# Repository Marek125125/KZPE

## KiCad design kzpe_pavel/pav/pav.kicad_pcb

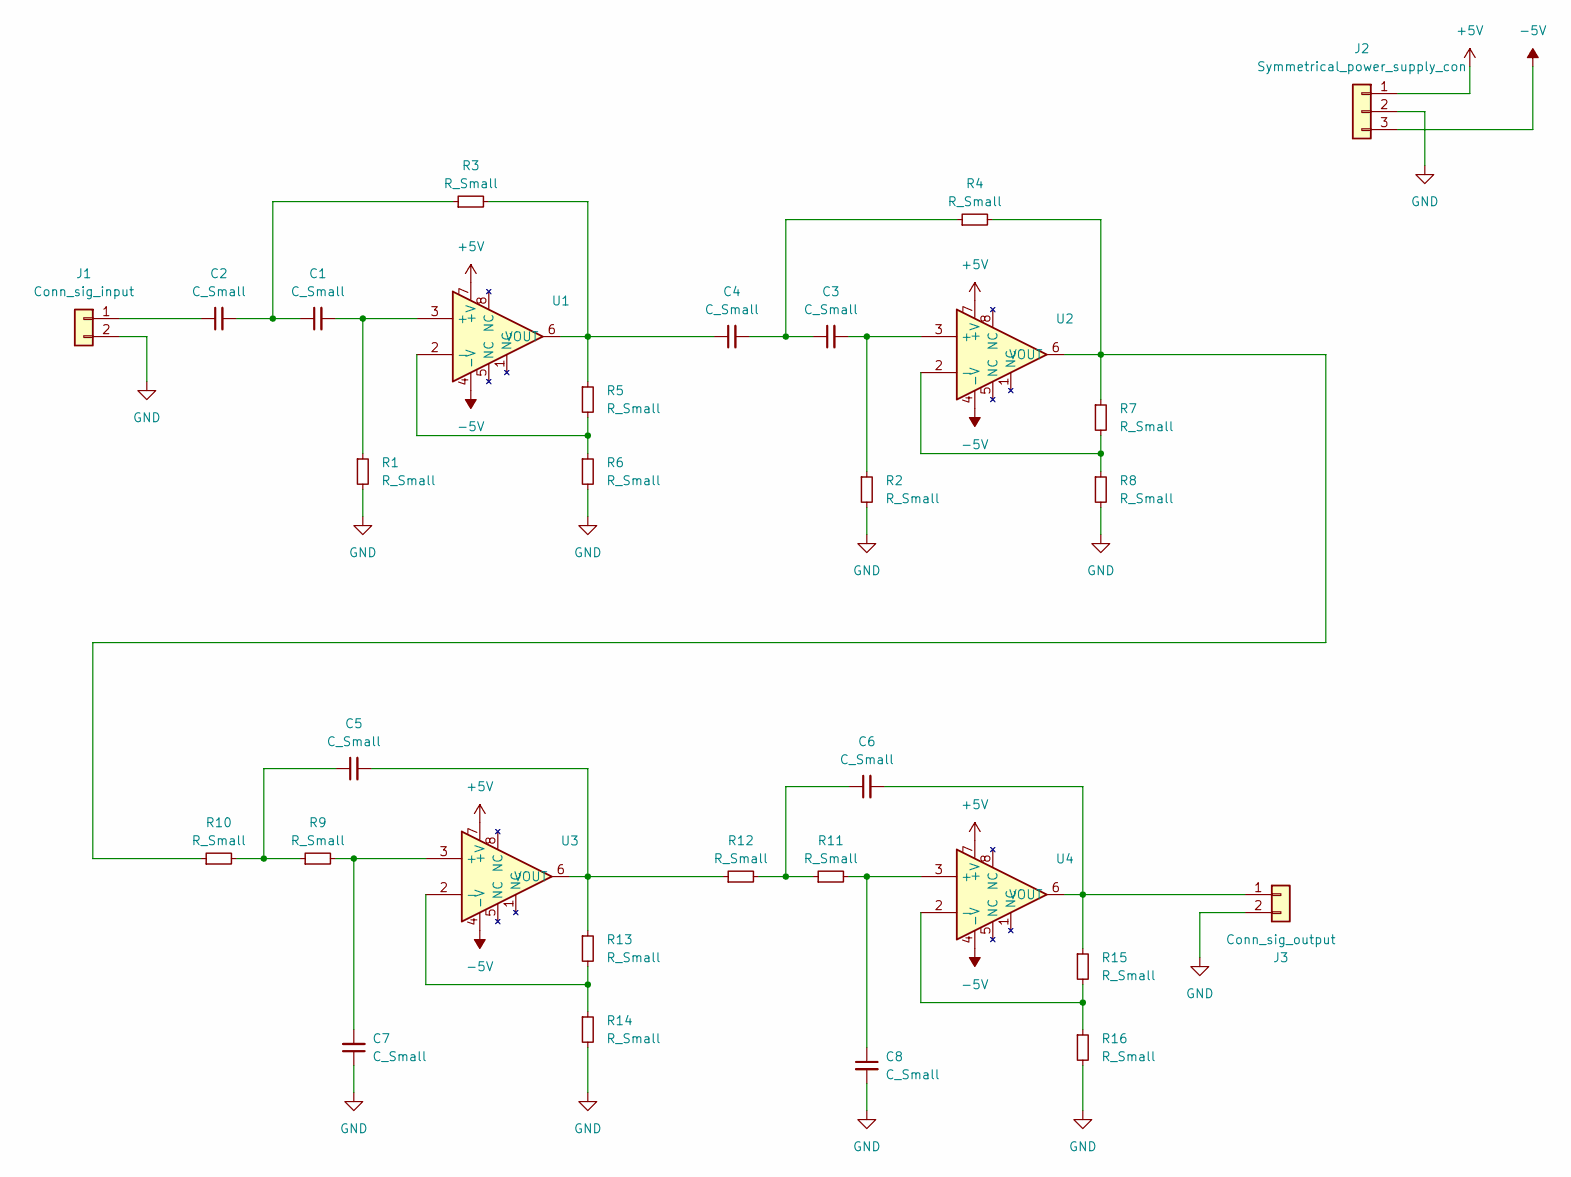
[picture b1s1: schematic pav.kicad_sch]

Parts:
C1, C2, C3, C4, C5, C6, C7, C8: C_Small; CP_Radial_D4.0mm_P2.00mm
J1: Conn_sig_input; JWT_A3963_1x02_P3.96mm_Vertical
J2: Symmetrical_power_supply_con; JST_EH_B3B-EH-A_1x03_P2.50mm_Vertical
J3: Conn_sig_output; JWT_A3963_1x02_P3.96mm_Vertical
R1, R2, R3, R4, R5, R6, R7, R8, R9, R10, R11, R12, R13, R14, R15, R16: R_Small; R_Axial_DIN0204_L3.6mm_D1.6mm_P7.62mm_Horizontal
U1, U2, U3, U4: DIP794W56P254L959H533Q8N

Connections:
+5V: J2.1, U1.7 (+V), U2.7 (+V), U3.7 (+V), U4.7 (+V)
-5V: J2.3, U1.4 (-V), U2.4 (-V), U3.4 (-V), U4.4 (-V)
GND: C7.1, C8.2, J1.2, J2.2, J3.2, R1.2, R2.2, R6.2, R8.2, R14.2, R16.2
unnamed: C1.1, C2.2, R3.1
unnamed: C3.1, C4.2, R4.1
unnamed: C5.1, R9.1, R10.2
unnamed: C6.1, R11.1, R12.2
unnamed: C2.1, J1.1
unnamed: C6.2, J3.1, R15.1, U4.6 (VOUT)
unnamed: C1.2, R1.1, U1.3 (+)
unnamed: C4.1, R3.2, R5.1, U1.6 (VOUT)
unnamed: C3.2, R2.1, U2.3 (+)
unnamed: R7.2, R8.1, U2.2 (-)
unnamed: R4.2, R7.1, R10.1, U2.6 (VOUT)
unnamed: C7.2, R9.2, U3.3 (+)
unnamed: R13.2, R14.1, U3.2 (-)
unnamed: C5.2, R12.1, R13.1, U3.6 (VOUT)
unnamed: C8.1, R11.2, U4.3 (+)
unnamed: R15.2, R16.1, U4.2 (-)

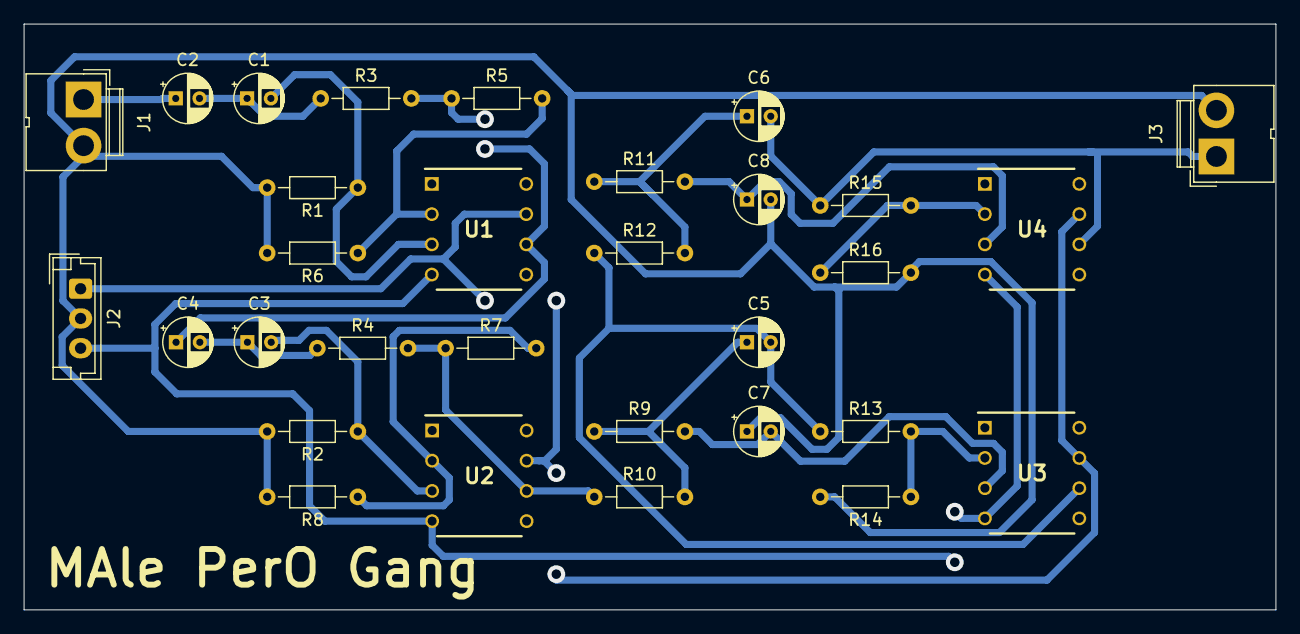
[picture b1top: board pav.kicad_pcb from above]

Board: 2 copper layers, 105.2 x 49.2 mm, 31 parts (0 on the bottom side), 19 nets.

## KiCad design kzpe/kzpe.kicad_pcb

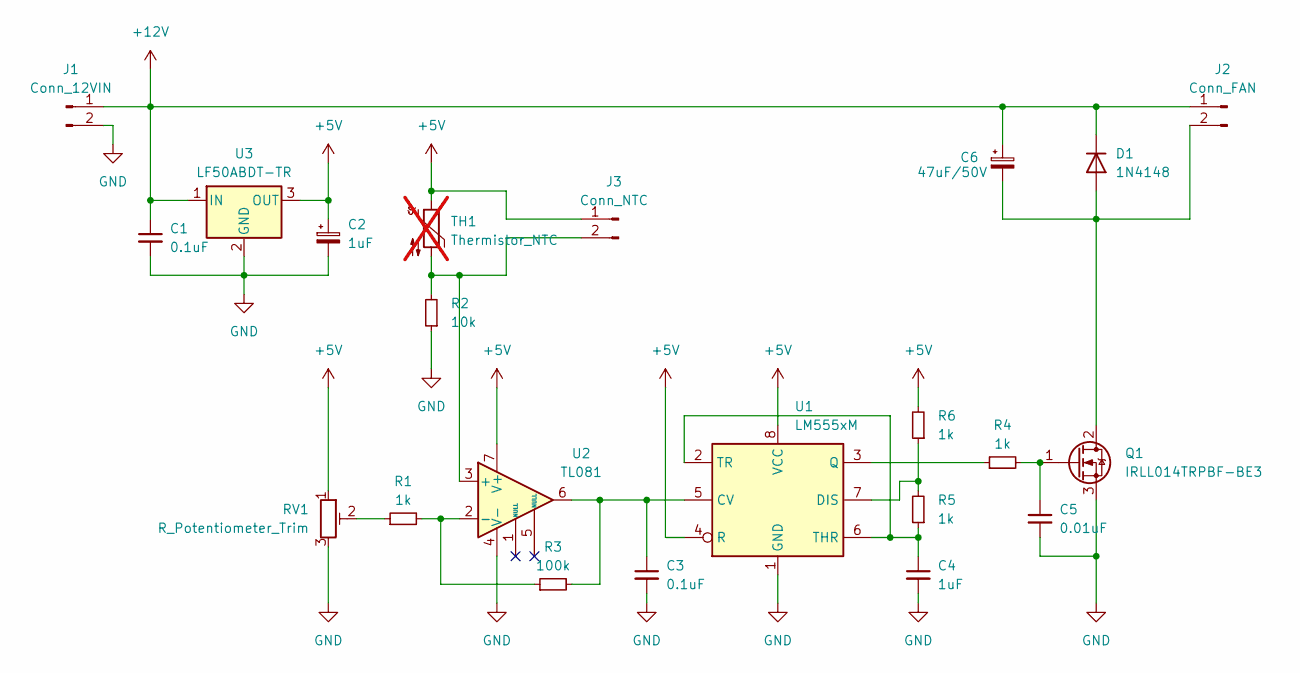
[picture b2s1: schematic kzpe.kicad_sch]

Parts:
C1, C3: 0.1uF; C_0402_1005Metric
C2, C4: 1uF; C_0402_1005Metric
C5: 0.01uF; C_0402_1005Metric
C6: 47uF/50V; CP_Elec_4x4.5
D1: 1N4148; D_0402_1005Metric
J1: Conn_12VIN; SolderWire-1.5sqmm_1x02_P6mm_D1.7mm_OD3mm
J2: Conn_FAN; SolderWire-1.5sqmm_1x02_P6mm_D1.7mm_OD3mm
J3: Conn_NTC; SolderWire-1.5sqmm_1x02_P6mm_D1.7mm_OD3mm
Q1: IRLL014TRPBF-BE3; SOT230P700X180-4N
R1, R4, R5, R6: 1k; R_0402_1005Metric
R2: 10k; R_0402_1005Metric
R3: 100k; R_0402_1005Metric
RV1: R_Potentiometer_Trim; Potentiometer_Bourns_3224J_Horizontal
TH1: Thermistor_NTC; R_0402_1005Metric; not fitted
U1: LM555xM; SOIC127P600X175-8N
U2: TL081; SOIC127P600X175-8N
U3: LF50ABDT-TR; TO228P972X240-3N

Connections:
+5V: C2.1, J3.1, R6.2, RV1.1, TH1.1, U1.4 (R), U1.8 (VCC), U2.7 (V+), U3.3 (OUT)
+12V: C1.1, C6.1, D1.1 (K), J1.1, J2.1, U3.1 (IN)
GND: C1.2, C2.2, C3.2, C4.2, C5.2, J1.2, Q1.3 (S), R2.1, RV1.3, U1.1 (GND), U2.4 (V-), U3.2 (GND)
unnamed: C6.2, D1.2 (A), J2.2, Q1.2 (D)
unnamed: J3.2, R2.2, TH1.2, U2.3 (+)
unnamed: C5.1, Q1.1 (G), R4.2
unnamed: R1.1, RV1.2
unnamed: C3.1, R3.2, U1.5 (CV), U2.6
unnamed: R5.2, R6.1, U1.7 (DIS)
unnamed: R4.1, U1.3 (Q)
unnamed: C4.1, R5.1, U1.2 (TR), U1.6 (THR)
unnamed: R1.2, R3.1, U2.2 (-)

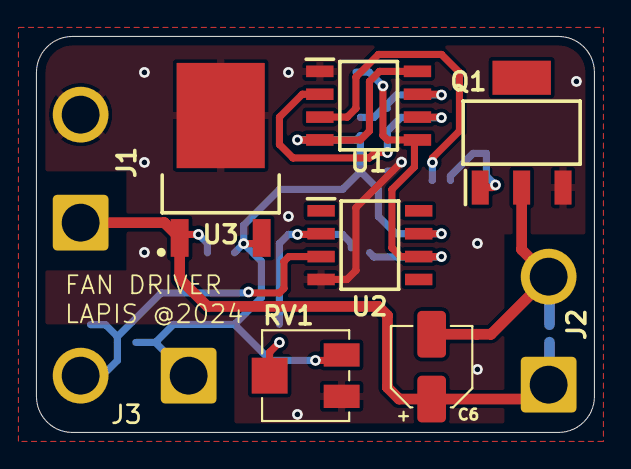
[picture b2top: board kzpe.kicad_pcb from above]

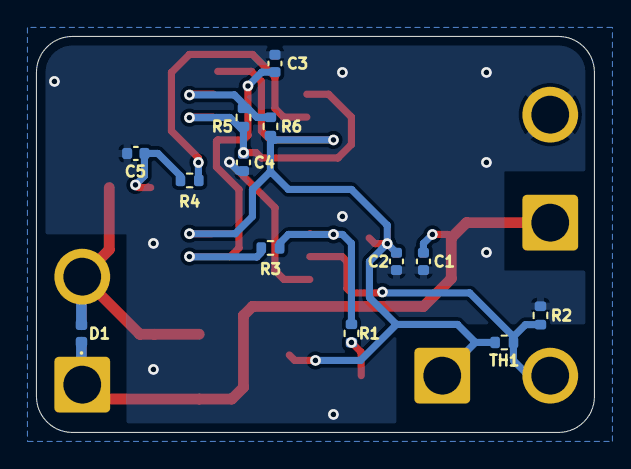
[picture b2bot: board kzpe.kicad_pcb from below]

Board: 2 copper layers, 31.0 x 22.0 mm, 22 parts (13 on the bottom side), 12 nets.

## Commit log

2024-12-02 init_kzpe
2024-12-09 0912
2024-12-10 1012
2024-12-11 1112
2024-12-13 1312
2024-12-13 1312v2
2024-12-13 1312v3
2024-12-13 1312v4
